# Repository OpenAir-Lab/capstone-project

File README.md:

<h1 align="center">
<<<<<<< HEAD
  <a href="https://github.com/OpenAir-Lab/capstone-project">
    
=======
  <a href="https://github.com/GITHUB_USERNAME/REPO_SLUG">
    
>>>>>>> 1358599 (docs: organized REV A and REV B pcb and schematic files and put them into their relavent folders)
  </a>
</h1>

<div align="center">
  OpenAir Lab – Modular Handheld Radio Development Kit  
  <br />
  <a href="#about"><strong>Explore the project »</strong></a>
  <br /><br />
<<<<<<< HEAD
  <a href="https://github.com/OpenAir-Lab/capstone-project/issues/new?labels=bug&template=01_BUG_REPORT.md&title=bug%3A+">Report a Bug</a>
  ·
  <a href="https://github.com/OpenAir-Lab/capstone-project/issues/new?labels=enhancement&template=02_FEATURE_REQUEST.md&title=feat%3A+">Request a Feature</a>
  ·
  <a href="https://github.com/OpenAir-Lab/capstone-project/issues/new?labels=question&template=04_SUPPORT_QUESTION.md&title=support%3A+">Ask a Question</a>
=======
  <a href="https://github.com/GITHUB_USERNAME/REPO_SLUG/issues/new?labels=bug&template=01_BUG_REPORT.md&title=bug%3A+">Report a Bug</a>
  ·
  <a href="https://github.com/GITHUB_USERNAME/REPO_SLUG/issues/new?labels=enhancement&template=02_FEATURE_REQUEST.md&title=feat%3A+">Request a Feature</a>
  ·
  <a href="https://github.com/GITHUB_USERNAME/REPO_SLUG/issues/new?labels=question&template=04_SUPPORT_QUESTION.md&title=support%3A+">Ask a Question</a>
>>>>>>> 1358599 (docs: organized REV A and REV B pcb and schematic files and put them into their relavent folders)
</div>

<div align="center">

<<<<<<< HEAD

=======

>>>>>>> 1358599 (docs: organized REV A and REV B pcb and schematic files and put them into their relavent folders)

</div>

---

## **About**

OpenAir Lab is an **open-source, modular handheld ham-radio development kit** designed to expose and teach all fundamental subsystems of a portable transceiver. Unlike commercial “black-box” radios, this platform separates RF, MCU, audio, power, and HMI into independent **Modulinos** connected through standardized EYESPI and I²C interfaces.

<<<<<<< HEAD
The system’s core is an **ESP32-WROVER-E** MCU hosting RF control, audio streaming, display driving, and power-management logic. 

Subsystems include:

- **RF modulino:** TI CC1200 sub-GHz transceiver  

- **HMI modulino:** 1.9" ST7789 TFT via EYESPI, keypad, user buttons, rotary encoder  

- **Audio modulino:** ICS-43434 digital MEMS microphone + MAX98357A I²S amplifier 

- **Power modulino:** STUSB4500 USB-PD, BQ25622 charger, fuel gauge  

- **Control plane:** I²C expander for low-rate signals (LEDs, keypad, resets, alerts)

=======
The system’s core is an **ESP32-WROVER-E** MCU hosting RF control, audio streaming, display driving, and power-management logic. Subsystems include:

- **RF modulino:** TI CC1200 sub-GHz transceiver  
- **HMI modulino:** 1.9" ST7789 TFT via EYESPI, keypad, user buttons, rotary encoder  
- **Audio modulino:** ICS-43434 digital MEMS microphone + MAX98357A I²S amplifier  
- **Power modulino:** STUSB4500 USB-PD, BQ25620 charger, fuel gauge  
- **Control plane:** I²C expander for low-rate signals (LEDs, keypad, resets, alerts)

>>>>>>> 1358599 (docs: organized REV A and REV B pcb and schematic files and put them into their relavent folders)
Purpose:  
• Provide a hands-on educational platform for embedded, RF, and systems engineering  
• Enable modular experimentation and rapid firmware iteration  
• Deliver a working open-source handheld radio for expo demonstration  

---

### **Built With**

- **ESP32-WROVER-E** (dual-core 240 MHz, Wi-Fi/BT, PSRAM)
- **CC1200 Sub-GHz RF Transceiver**  
- **Adafruit 1.9" ST7789 TFT Display + EYESPI connector**  
- **ICS-43434 MEMS microphone**  
- **MAX98357A I²S amplifier**  
- **STUSB4500 USB-PD controller**  
- **BQ25620 battery management IC**  
- **I²C GPIO Expander (TCA9539/MCP23017)**  
- **FreeRTOS-style firmware architecture** (timers, ISRs, tasks)

---

## **Getting Started**

### **Prerequisites**

The project requires:

- ESP32 toolchain (ESP-IDF or PlatformIO/Arduino)
- EYESPI breakout for the TFT display (18-pin FPC)
- Access to I²C and SPI buses for CC1200, audio, and PD controller  
- 3.3 V power supply capable of ≥500 mA for ESP32-WROVER-E  

### **Installation**

1. Clone the repository  
2. Open the firmware directory in ESP-IDF or PlatformIO  
3. Connect the MCU modulino to UART (use BOOT/EN buttons on custom boards)  
4. Build and flash the firmware  
5. Connect modulinos via EYESPI and I²C cables  

---

## **Usage**

Firmware operates through **interrupt-driven inputs**, **FreeRTOS tasks**, and **timers**:

- Keypad, encoder, and PTT interrupts update application state  
- CC1200 provides frequency control, RX/TX switching, and RSSI sampling  
- TFT displays live frequency, signal strength, battery state, settings  
- Tasks handle display refresh, PTT timeout, and periodic battery polling  
- Audio subsystem processes microphone data and sends I²S audio to amplifier  

---

## **Roadmap**

See open issues:  
<<<<<<< HEAD
https://github.com/OpenAir-Lab/capstone-project/issues
=======
https://github.com/GITHUB_USERNAME/REPO_SLUG/issues
>>>>>>> 1358599 (docs: organized REV A and REV B pcb and schematic files and put them into their relavent folders)

Current priorities:

- Finalize pin mapping across all modulinos  
- Complete MCU subsystem schematic in KiCad  
- Implement full FreeRTOS task architecture  
- Bring-up and test Rev A PCB  
- Assemble proof-of-concept handheld radio for expo  

---

## **Support**

Contact the maintainers via:

- GitHub issues (for questions):  
<<<<<<< HEAD
  https://github.com/OpenAir-Lab/capstone-project/issues/new?labels=question  
=======
  https://github.com/GITHUB_USERNAME/REPO_SLUG/issues/new?labels=question  
>>>>>>> 1358599 (docs: organized REV A and REV B pcb and schematic files and put them into their relavent folders)
- Maintainer contact info on GitHub profile  

---

## **Project Assistance**

If you want to support the project:

- Star the repo ⭐  
- Share the project  
- Contribute hardware, firmware, or documentation improvements  

---

## **Contributing**

Contributions are welcome!  
<<<<<<< HEAD
Please review `Documentation/Contributing.md` before submitting a pull request.
=======
Please review `docs/CONTRIBUTING.md` before submitting a pull request.
>>>>>>> 1358599 (docs: organized REV A and REV B pcb and schematic files and put them into their relavent folders)

---

## **Authors & Contributors**

Project created and maintained by the OpenAir Lab MCU & Systems Integration Team.  
Full contributor list:  
<<<<<<< HEAD
https://github.com/OpenAir-Lab/capstone-project/contributors
=======
https://github.com/GITHUB_USERNAME/REPO_SLUG/contributors
>>>>>>> 1358599 (docs: organized REV A and REV B pcb and schematic files and put them into their relavent folders)

---

## **Security**

Provided “as is” with no warranty.  
See `docs/SECURITY.md` for disclosure instructions.

---

## **License**

Licensed under the **MIT License**.  
See `LICENSE` for details.

---

## **Acknowledgements**

This project uses or references:

- **Espressif – ESP32-WROVER-E Datasheet & Technical Reference Manual**  
- **Adafruit – ST7789 TFT & EYESPI Documentation**  
- **Texas Instruments – CC1200 RF Transceiver**  
- **STMicroelectronics – STUSB4500 USB-PD Controller**  
- **TDK/Knowles – ICS-43434 MEMS Microphone**  
- **MAX98357A I²S Amplifier Datasheet**

We also acknowledge the design documentation for the OpenAir Lab subsystem interface and pin mapping.

---

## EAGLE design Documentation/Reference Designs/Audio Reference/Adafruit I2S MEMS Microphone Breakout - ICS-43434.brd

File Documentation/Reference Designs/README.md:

# Reference Designs

Maintained in this documentation directory are the reference designs utilized in the "Schematic Recapture" process. 

## Schematic Recapture

Schematic recapture is the process of going from either provided vendor-specific design files created by their preferred Electronic Design Assistant (EDA) or provided generated fabrication outputs, i.e. GERBER and Excellon/NC Drill files.

The intent is to go from fabrication outputs or EDA-specific project files to a KiCAD project. 
- This means converting imported symbols into 'real' KiCAD symbols. If first-party symbols are not available or are incomplete, the next preference is for KiCAD built-in libraries.
- This also means converting imported footprints into 'real' KiCAD footprints. Many footprint libraries built-in to KiCAD lack 3D models and thus 3rd party services have been used to make the footprint information more complete.

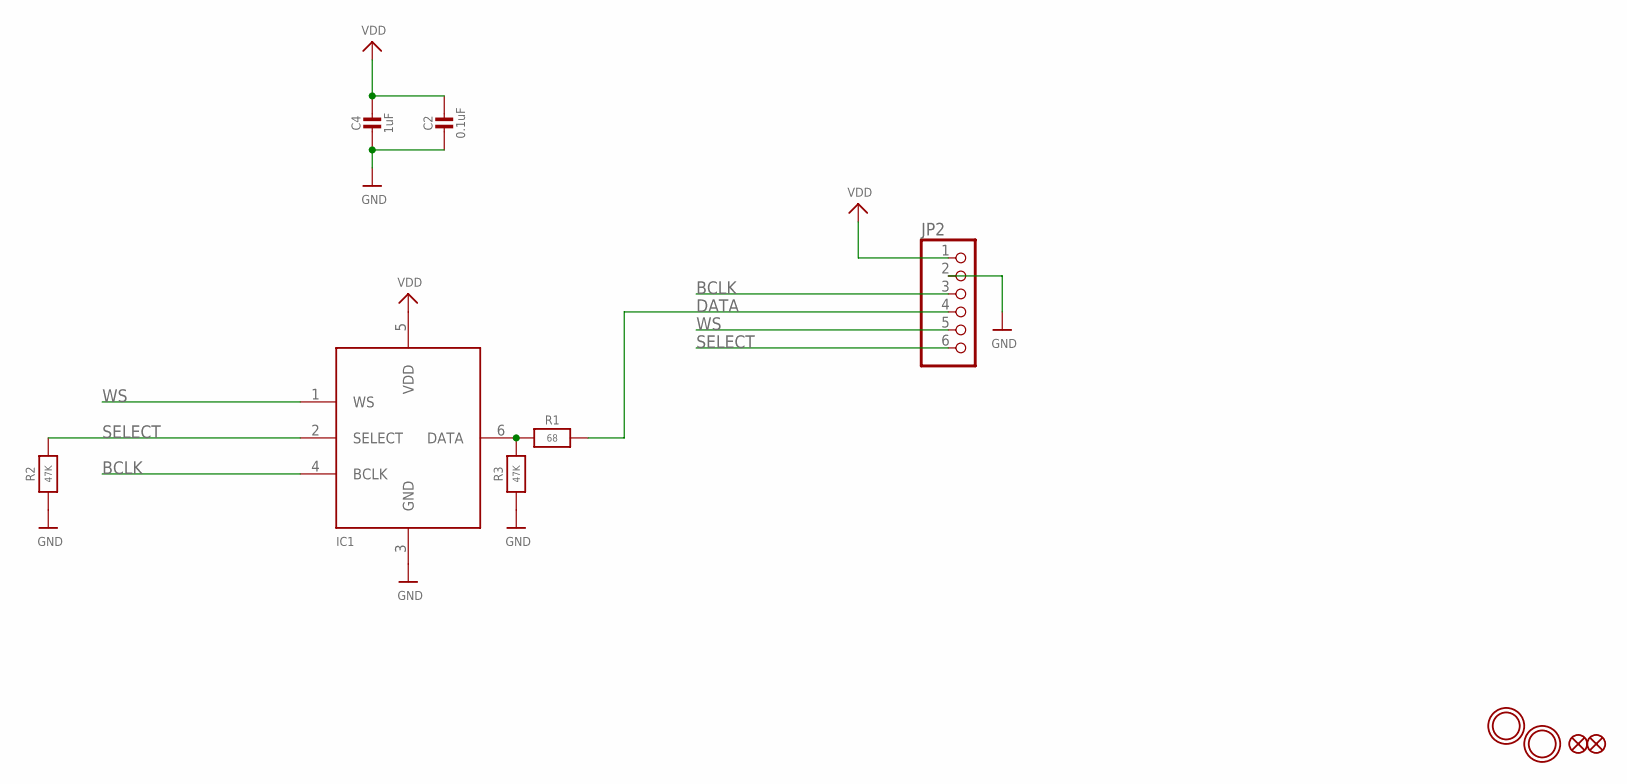
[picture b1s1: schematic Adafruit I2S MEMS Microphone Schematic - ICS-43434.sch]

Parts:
C2: 0.1uF; 0603-NO
C4: 1uF; 0603-NO
FID1, FID2: FIDUCIAL_0.5MM
IC1: ICS-43434; SPH0645LM4H
JP2: HEADER-1X6ROUND; 1X06_ROUND
R1: 68; 0603-NO
R2, R3: 47K; 0603-NO
U$6, U$12: MOUNTINGHOLE2.5; MOUNTINGHOLE_2.5_PLATED

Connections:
BCLK: IC1.4 (BCLK), JP2.3
DATA: JP2.4, R1.2
GND: C2.2, C4.2, IC1.3 (GND), JP2.2, R2.1, R3.1
unnamed: IC1.6 (DATA), R1.1, R3.2
SELECT: IC1.2 (SELECT), JP2.6, R2.2
VDD: C2.1, C4.1, IC1.5 (VDD), JP2.1
WS: IC1.1 (WS), JP2.5

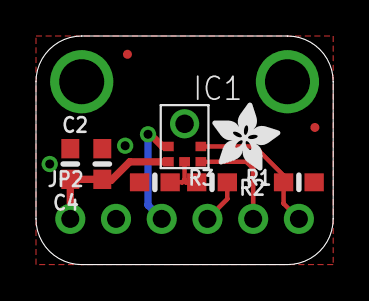
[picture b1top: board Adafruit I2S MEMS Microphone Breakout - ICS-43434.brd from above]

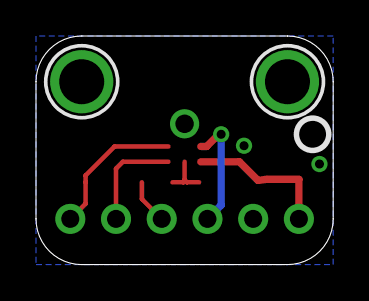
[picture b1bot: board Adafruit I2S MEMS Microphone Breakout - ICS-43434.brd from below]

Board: 2 copper layers, 16.5 x 12.7 mm, 23 parts (11 on the bottom side), 7 nets.

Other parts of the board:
PLABEL0: PLABEL0
PLABEL1: PLABEL1
PLABEL2: PLABEL2
PLABEL3: PLABEL3
PLABEL4: PLABEL4
PLABEL5: PLABEL5
PLABEL7: PLABEL7
PLABEL8: PLABEL8
PLABEL9: PLABEL9
PLABEL10: PLABEL10
U$5: ADAFRUIT_3.5MM
U$13: PCBFEAT-REV-040

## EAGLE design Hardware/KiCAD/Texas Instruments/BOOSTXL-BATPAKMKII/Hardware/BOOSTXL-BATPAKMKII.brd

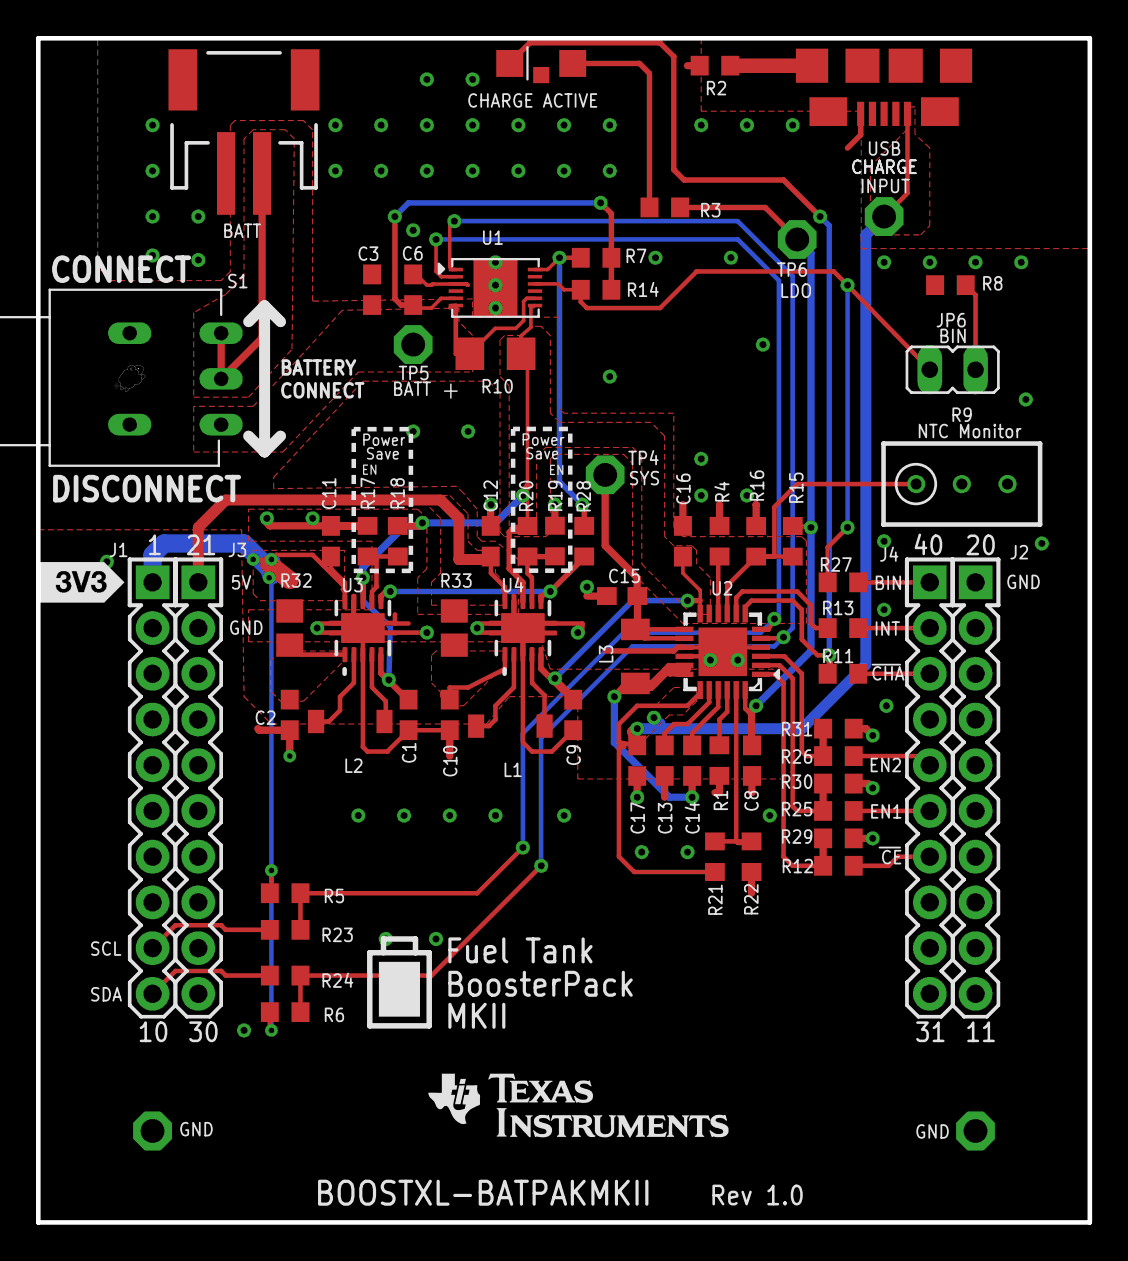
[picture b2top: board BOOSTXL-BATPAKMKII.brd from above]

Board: 2 copper layers, 58.4 x 65.8 mm, 73 parts (0 on the bottom side), 46 nets.

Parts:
BATT: JST-2-SMD
C1, C2, C9, C10: 10uF; C0603
C3, C8, C13, C16, C17: 1uF; C0603
C6, C11, C12: 0.47uF; C0603
C14: 33nF; C0603
C15: 22uF; C0603
DRAW3: LOGO-ROCKET-10X7MM-BRD
J1: 1X10
J2, J3, J4: 1X10-J3
JP6: JP1
L1, L2: 2.2uH; VLF4102A
L3: 1uH; L3216C
LED2: YELLOW; RIGHTANGLE_1208
R1: 270; R0603
R2, R11, R12, R13, R25, R26, R27, R28: 0; R0603
R3: 1k; R0603
R4: 500; R0603
R5, R6, R7: 5.1k; R0603
R8, R18, R20, R29, R30, R31: 10K; R0603
R9: RTRIM3296W
R10: 0.01; R1206
R14: 1.8M; R0603
R15: 5.1K; R0603
R16: 7.5K; R0603
R17, R19: DNP; R0603
R21: 274k; R0603
R22: 100k; R0603
R23, R24: 200; R0603
R32, R33: 0R; R0805
S1: TS-6_SPDT
TP1, TP2, TP3, TP4, TP5, TP6: PTR1PAD1-13; P1-13
U1: BQ27441DRZ; DRZ12
U2: BQ24250RGE; TI_RGE24
U3: TPS63001; DRC-S-PVSON-N10
U4: TPS63002; DRC-S-PVSON-N10
U$1: SILK_3V3_TAG
U$2: MS_(TM)
U$4: LOGO16_TPLACE
USB: CONN_USB_MICRO_B; USB_MICRO_B_SMT

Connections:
3V3: C2.1, R32.1, U3.1
5V: C12.1, J3.21, R33.2, U4.10
!BAT_LOW: R28.2, U3.6, U4.6
!CE: R12.1, R29.2, U2.1
!CE!_LP: J4.27, R12.2
!CHARGE: LED2.CATHODE, R11.1, U2.7
!CHARGE_LP: J4.23, R11.2
+3V3: C11.1, J1.1, R5.2, R6.2, R32.2, U3.10
+5V_CHARGE: C17.1, R21.1, TP1.TP, U2.19, USB.1
BIN: JP6.1, R14.1, R27.1, U1.10
BIN_LP: J4.21, R27.2
CS_IN/SYS: C15.1, L3.2, TP4.TP, U2.13, U2.14
EN1: R25.1, R30.2, U2.2
EN1_LP: J4.26, R25.2
EN2: R26.1, R31.2, U2.3
EN2_LP: J4.25, R26.2
GND: BATT.1, C1.2, C2.2, C3.2, C6.2, C8.2, C9.2, C10.2, C11.2, C12.2, C13.2, C15.2, C16.2, C17.2, J2.21, J3.22, R1.2, R2.2, R4.1, R8.1, R9.2, R9.3, R16.1, R17.1, R19.1, R22.2, R29.1, R30.1, R31.1, TP2.TP, TP3.TP, U1.3, U1.P$1, U2.4, U2.15, U2.16, U2.P$1, U3.3, U3.9, U4.3, U4.9, USB.5
GPOUT: R7.1, R28.1, U1.12
INT: R13.1, U2.8
INT_LP: J4.22, R13.2
LDO: C8.1, R3.2, R15.1, TP6.TP, U2.24
unnamed: L2.P$3, U3.4
unnamed: L2.P$1, U3.2
unnamed: L1.P$3, U4.4
unnamed: JP6.2, R8.2
unnamed: LED2.ANODE, R3.1
unnamed: L1.P$1, U4.2
unnamed: R9.1, R15.2, R16.2, U2.9
unnamed: R21.2, R22.1, U2.23
unnamed: C13.1, U2.20
unnamed: C14.1, U2.21
unnamed: C14.2, L3.1, U2.17, U2.18
unnamed: BATT.2, S1.2, S1.3
unnamed: R4.2, U2.10
unnamed: R2.1, USB.P$9
unnamed: R17.2, R18.1, U3.7
unnamed: R19.2, R20.1, U4.7
unnamed: R1.1, U2.22
unnamed: C10.1, R33.1, U4.1
PACK+: C3.1, R10.2, S1.1, TP5.TP, U1.6, U1.8
PACK+_OUT: C1.1, C9.1, C16.1, R10.1, R18.2, R20.2, U1.7, U2.11, U2.12, U3.5, U3.8, U4.5, U4.8
SCL: R5.1, R23.1, U1.2, U2.6
SCL_LP: J1.9, R23.2
SDA: R6.1, R24.1, U1.1, U2.5
SDA_LP: J1.10, R24.2
VDD: C6.1, R7.2, R14.2, U1.5

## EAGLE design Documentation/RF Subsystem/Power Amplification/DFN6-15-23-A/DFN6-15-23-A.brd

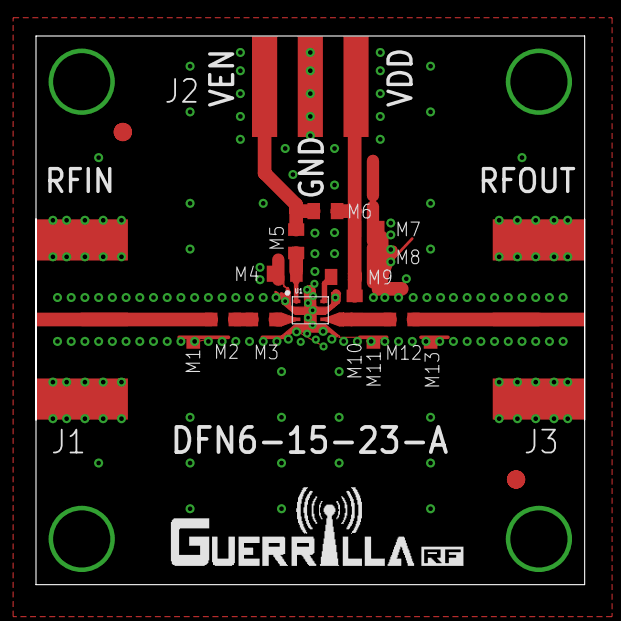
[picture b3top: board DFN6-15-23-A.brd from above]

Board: 4 copper layers, 30.5 x 30.5 mm, 22 parts (0 on the bottom side), 12 nets.

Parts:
DRILEGEND: DRILEGEND
FID: GRF_LOCAL_FIDUCIAL
FID@1: GRF_LOCAL_FIDUCIAL
J1: MOLEX_KK_HEADER_3-PIN_0.100-INCH
M1, M11, M13: 0.5pF; RCL_C0402_GRF
M2, M3, M12: 100pF; RCL_C0402_GRF
M4: 100pF; C0402
M5, M6, M9: 0 Ohm; R0402
M7, M8: 0.1uF; C0402
M10: 220nH WW; L0402
RFIN: SMA-142-0701-801/806; J502-ND-142-0701-801/806
RFOUT: SMA-142-0701-801/806; J502-ND-142-0701-801/806
U$1: DFN-6_GENERICUPDATED; DFN-6_1.5X1.5MM_FIXED
U$2, U$3: GRF_LOCAL_FIDUCIAL

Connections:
FID: FID.FID, FID@1.FID
FID1: U$2.FID, U$3.FID
GND: J1.GND, M1.2, M4.2, M7.2, M8.2, M11.2, M13.2, RFIN.G@1, RFIN.G@2, RFIN.G@3, RFIN.G@4, RFOUT.G@1, RFOUT.G@2, RFOUT.G@3, RFOUT.G@4, U$1.2, U$1.5, U$1.GND
unnamed: M3.2, U$1.3
unnamed: J1.VENABLE, M5.2, M6.1
unnamed: M1.1, M2.1, RFIN.1
unnamed: M4.1, M5.1, U$1.1
unnamed: M10.2, M11.1, M12.2, U$1.4
unnamed: M12.1, M13.1, RFOUT.1
unnamed: M9.1, U$1.6
unnamed: J1.VDD, M6.2, M7.1, M8.1, M9.2, M10.1
unnamed: M2.2, M3.1

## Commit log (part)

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2025-07-18 Create WROVER-documentation.md
    File for documentation purposes
2025-07-18 Update WROVER-documentation.md
    content
2025-07-19 feat: begin recapture & document RF Power Amplifier
2025-07-19 feat: begin recapture & document RF Transceiver
2025-07-19 feat: recapture and documentation on BMS IC's
2025-07-21 docs: I2S Protocol #13
2025-07-22 feat: begin annotating eval module BoM #7
2025-07-22 feat: include past meeting notes
2025-07-22 Create PDR-July 21.md
    Meeting notes. Everyone please look at this and add to it !!
2025-07-26 Doc: Audio Amplifier Schematic
2025-08-18 feat: begin system testbed schematic capture
2025-08-19 chore: co-locate vendor evaluation recaptures #6
2025-08-19 feat: capture Switched Analog Volume Potentometer and Switched Quadrate Rotary Encoder #15
2025-08-19 feat: capture 4x4 Keypad Module #15
2025-08-19 feat: begin importing Battery Management System capture in new power subsystem sheet #3 #21
2025-08-19 feat: begin RF subsystem capture #7 #16
2025-08-20 feat: complete recapture of Adafruit Mic Module
2025-08-21 feat: begin dedicated sheets for RF switch throws, refine PA RFIC symbol #34
2025-08-22 feat: refine rf subsystem sheet, specify band selection from two tuned PAs #34
2025-08-25 chore: revise RF switch symbol description #34
2025-08-25 feat: complete RF switches, revise RF sheet structure #34
2025-08-25 feat: assign RF netclass to RF signal paths #34
2025-08-27 Create August 25 - First Meeting of Senior Design 2.md
    8.26 Meeting with the Team - please read
2025-08-29 feat: capture EYESPI display connectors #15
2025-08-29 feat: plot system testbed #41
2025-08-29 feat: re-sized PSU box KiCAD Runthrough Fixes #30
2025-09-02 docs: added a some brief notes taken in the workflow meetig (these will need to be expanded upon)
2025-09-03 feat: testing commit
2025-09-03 feat: import board stackup of OSHPark Prototype Service #57
2025-09-03 fix: create real EYESPI FPC connector symbol and footprint #57
2025-09-03 feat: assign 0603 passive component footprints #32 #34
2025-09-03 chore: ignore .DS_Store files
2025-09-03 not sure what changes were made for this but I'm committing for posterity
2025-09-04 docs: draft recapture of Modulino for Templating #57
2025-09-04 fix: move port expander over to HMI schematic #15 #33
2025-09-04 fix: relabel TRX GPIOs to breakout over EYESPI #34 #65
2025-09-04 docs: Pin Mapping Table for MCU and all interconnected subsystems
2025-09-04 Rename Pin Mapping Table to Pin Mapping Table.md
    markdown file
2025-09-05 feat: Testing Sync
2025-09-06 chore: set pad size defaults
2025-09-06 feat: create Hello World in ESP-IDF using PlatformIO
2025-09-06 datasheets and added esp32 symbol
2025-09-06 fix: added WROVER symbol to project library and schematic
2025-09-07 Update Pin Mapping Table.md
    need to find alternative for STUSB4500 GPIO
2025-09-08 audio-subsystem schematic update Audio PCB Fixes #32
2025-09-09 feat: update MCU schematic
2025-09-09 fix: add power devices to library
2025-09-09 fix: relocate sheets on testbench
2025-09-10 Feat(Library): Add batch of new power ICs
2025-09-11 feat: add RF switch with built-in decoder #65
2025-09-11 chore: pin project footprint library
2025-09-11 fix: remove mounting holes for unused HW-834 keypad #69
2025-09-11 fix: standardize size symbol pins of RF switch to 2.54mm #65
2025-09-11 feat: begin use of discrete diplexers over band select switches #65 feat: redraw rx/tx switching with built-in decode plus level shifting #34 feat: begin RF modulino testpoints #45
2025-09-11 chore: replot system testbed #41
2025-09-11 Update-Jumper-Schematic
2025-09-12 feat: capture Audio PCB #32 feat: begin I2S Pin Mapping and Interconnects #53
2025-09-12 fix: clarify labellng and pin head #32
2025-09-12 fix: rename #32
2025-09-12 fix: import RF sheet contents #65
2025-09-12 feat: move modulino interconnects to root sheet #57
2025-09-12 fix: correct input and output for labels #51
2025-09-12 fix: remove EYESPI from HMI sheet #69
2025-09-12 feat: pin relabel #63
2025-09-12 fix: reannotate and resolve power nets #51
2025-09-12 feat: schematic capture #63
2025-09-13 fix: Cleaned up structure of BMS PSU Schematic Capture Fixes #51
2025-09-13 Create Workflow Runthrough #2.md
    Summary of what was covered in Weekly Workflow 2
2025-09-13 Create Workflow Runthrough #4.md
    summary of workflow 4 - advanced PCB tools
2025-09-13 Create september 4 - Team Slide Review.md
    Slide review from the week we did not have an advisor meeting
2025-09-13 feat: added WROVER footprint to project library & symbol
2025-09-13 feat: added WROVER footprint to project library & symbol - MCU Schematic capture Fixes #63
2025-09-13 fix: fixing labels PSU Schematic Capture Fixes #51
2025-09-13 fix: reannotate schematics for pcb editor use #55
2025-09-14 Feat: Added ICs & Completed schematic for the other blocks
2025-09-14 Revert "Feat: Added ICs & Completed schematic for the other blocks"
    This reverts commit 5ccb9a6ab9d8f693594799fe98ca877545035d56.
2025-09-14 Fix: Changed IC positions
2025-09-14 Feat: Added footprint for TVS Diode
2025-09-18 fix: remove unused mounting holes for HW #69 fix: edit symbol fields of button matrix #69
2025-09-18 fix: recover audio schematic #70
2025-09-18 feat: swap to vertical rotary encoder used by Modulino Knob #69
2025-09-23 fix: allow for DRC use in PCB editor by successful reannotation
2025-09-24 feat: begin arduino framework instead of arduino component compatibility #12
2025-09-24 feat: include Adafruit ST7789 demo and begin #15
2025-09-24 feat: begin transceiver driver and capture command strobes #12
2025-10-02 feat: update pinouts for mcu #53
2025-10-12 Create Oct 9 Team Meeting.md
    Slide Review meeting (members only)
2025-10-16 Create Oct 14 Workshop - PlatformIO.md
    PlatformIO and next steps
2025-10-22 chore: remove .DS_Store files
2025-10-22 chore: co-locate datasheets
2025-10-22 chore: co-locate reference design files
2025-10-22 chore: migrate Adafruit reference design to documentation
2025-10-22 chore: remove .DS_Store
2025-10-22 chore: move TI reference designs to documentation
2025-10-22 feat: use symlinks to common project KiCAD footprint library
2025-10-22 feat: include interactive bill of materials for all REV A modulinos
2025-10-22 chore: move Guerrilla RF reference designs to documentation
2025-10-22 chore: replot system testbed schematic describing all modulinos #55
2025-10-22 feat: begin all modulino board directories
2025-10-22 feat: separate RF subsystems for testing using SMA edge launches in testbed KiCAD project #65 #34 #45
2025-10-22 feat: begin USB-PD modulino hardware directory
2025-10-22 docs: begin describing reference design use and "schematic recapture" process #57 #48
2025-10-24 fix: clarify naming of sck pin configuration #82
2025-10-28 feat: begin demo selection code #12 #41
2025-10-28 feat: add config registers and begin single access plus command strobes #45 #81 #82
2025-10-29 chore: added MCU modulino Rev A PCB files to testbed
2025-10-29 feat: include Adafruit PC8575 library and begin port expander #82 #83
2025-10-29 Update Pin Mapping Table.md
    fix: changed reassigned pin numbers
2025-10-31 chore: added additional Rev A PCB file to MCU modulino
2025-11-01 chore: keep BusIO dependency
2025-11-01 feat: create skyworks switch driver #45 #82
2025-11-01 feat: Rotary Encoder Interfacing with HMI Menue #86
2025-11-03 chore: moved Adafruit display sample code from main #86
2025-11-03 feat: refine switch demo and begin amplifier demo #45 #82
2025-11-03 docs: include amplifier startup sequencing #45 #82
2025-11-03 feat: reflect new libraries and begin moving demos #41
2025-11-04 feat: allow passing in PCF port expander instance #83 fix: remove misinterpreted PORT address map
2025-11-04 feat: assign control signals to RF port expander #82
2025-11-04 chore: test code for WROVER - i2c, spi, cores, gpios MCU Testing #83
2025-11-06 Audio PCB Modulino
2025-11-07 feat: move I2C scan debugging into port expander initialization
2025-11-14 Revert "Merge MCU branch with main"
2025-11-15 feat: get SPI transactions working for register access #81
2025-11-15 fix: migrate display updates away from switching logic #82
2025-11-15 chore: move init verification to prep for real transceiver demo #81 #82
2025-11-15 feat: establish display init and config chore: rename folder to display driver chip name
2025-11-16 feat: rewrite most demos for one-time device inits #82
2025-11-17 feat: Added PD Advertisement code PSU PCB Testing Fixes #38
2025-11-19 feat: improve debug printing and include more fonts #86
2025-11-19 feat: better integrate I2C scanner, improve debug printing, allow for storing name of expander #83 #86 #82
2025-11-19 feat: refactor device initialization routines for clarity, remove unused display demo code #86 feat: improve debug printing format and content for demo selection #12 #55
2025-11-19 feat: improve switch demo visuals and debug printing #82
2025-11-19 feat: improve debug printing, relocate interface setup routine #82
2025-11-24 chore: enhance debugging and comments
2025-11-24 fix: simplify access logic feat: begin cc1200 settings
2025-11-24 feat: add hmi and mcu modulinos
2025-11-27 feat: implement frequency deviation and symbol rate register value calculations #82 chore: update build flags to use C++20 language features
2025-11-27 fix: properly clear register fields #82
2025-11-27 feat: begin I2S device drivers
2025-12-01 HMI Firmware Adds to #86 feat: hmi/ui code for display and state update
2025-12-01 MCU Testing & Firmware #83 feat: task structure code and state update
2025-12-01 docs: MCU progress update and todos
2025-12-01 MCU Testing & Firmware Fixes #83 chore: test code for mcu
2025-12-01 fix: update main.cpp in MCU folder, kept separate from the firmware folder to avoid adding in errors before testing the code
2025-12-01 Feat: HMI Code HMI Firmware Fixes #86
2025-12-01 Rename HMI-code to HMI-code.cpp
    added .cpp to make it a C++ file
2025-12-01 Feat: Fuel gauge code (with comments)
2025-12-01 fix: modified function calls
2025-12-01 chore: ignore tests
2025-12-02 feat: improve driver interfacing, continue frequency programming #82
2025-12-02 chore: specify function declarations #82
2025-12-04 feat: mcu demo code and header files, still a work in progress MCU Testing & Firmware #83
2025-12-04 docs: updated Roadmap
2025-12-05 chore: organizes all files on mcu branch
2025-12-06 Audio Reference
2025-12-06 docs: organized REV A and REV B pcb and schematic files and put them into their relavent folders
2025-12-06 docs: added power modulino schematics for Rev A and Rev B
2025-12-06 docs: include device and connector datasheets
2025-12-06 fix: use C string over std::string in printf
2025-12-06 fix: correct RF expander and I2S0 pin assigment, set display rotation
2025-12-06 feat: refine cc1200 driver interface, begin I2S helpers #45
2025-12-06 chore: update VSCode workspace settings
2025-12-06 docs: update README
2025-12-06 docs: update all system schematics for project uniformity
2025-12-07 fix: provide return for playback #91
2025-12-07 feat: write manual calibration routine #82
2025-12-09 docs: addtl CC1200 active mode application note
2025-12-09 feat: begin RSSI freeRTOS timer and task, begin MainTask switch
2025-12-09 fix: change 3D model paths to be in project footprint library
2025-12-10 code: testing knob
2025-12-10 docs: added config code for knob test
2025-12-10 moved demo code
2025-12-12 feat: add BMS and Fuel Gauge libraries and usage
2025-12-12 feat: begin RSSI FreeRTOS Task structure
2025-12-12 feat: add keypad, begin rotary
2025-12-12 feat: taskify switch demo
2025-12-12 fix: begin use of fallback display demo
2025-12-21 fix: make bms task loop
2025-12-21 fix: make adafruit demo rtos friendlier
2025-12-21 chore: complete drawPowerdown tft update isolation
2025-12-21 fix: ensure initializers are blocking
2025-12-21 Revert "Revert "docs: organized REV A and REV B pcb and schematic files and put them into their relavent folders""
2026-02-16 fix: make adafruit display demo rtos friendlier
2026-02-16 feat: utilize fuel gauge and bms libraries
2026-02-16 feat: keypad and scanner routines
2026-02-16 fix: routine-ify using empty loop
2026-02-16 fix: refactor RSSI routine, correct port expander use

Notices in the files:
parts and their libraries:
microbuilder: This work is placed in the public domain, and may be freely used for commercial and non-commercial work with the following conditions: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
SparkFun: Licensing: CC v3.0 Share-Alike You are welcome to use this library for commercial purposes.
